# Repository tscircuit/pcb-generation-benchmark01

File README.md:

# PCB Generation Benchmark

Project scaffold for a paired dataset comparing three ways of producing PCB designs from the same prompts:

| Method ID | Workflow | Primary artifacts |
| --- | --- | --- |
| `tscircuit-codegen` | Generate tscircuit source code | Source, dependency lockfile, build outputs |
| `kicad-codegen` | Generate KiCad files directly or through recorded scripts/APIs | Native project, schematic, PCB, generation scripts |
| `kicad-computer-use` | Create and edit designs through KiCad's GUI | Native project, schematic, PCB, screenshots and action trace |

**Status: 10 draft prompts and a completed two-method generation pilot.** The [prompt catalog](prompts/README.md) includes easy, medium, and hard prompts with topic labels. The [pilot results](reports/2026-09-05-codegen-pilot-01/README.md) contain 20 generated schematic/PCB outcomes, retained candidates, previews, and raw validation reports. Computer use was excluded at the user’s request. Some generated designs have failing checks or unverified requirements; execution completion is not design acceptance. A deterministic rule scorer is implemented; reusable generation adapters/runner and scoring calibration remain future work.

## Layout

```text
prompts/                 Shared prompt catalog and per-prompt assets
configs/                 Experiment and environment templates
methods/                 Workflow contracts for the three methods
schemas/                 Record conventions for future validators
templates/               Copyable prompt, run, and evaluation records
data/runs/               Raw runs, organized by experiment/prompt/method/replicate
data/evaluations/        Separate evaluation records linked to run IDs
data/releases/           Future versioned dataset manifests
src/adapters/            Reserved for method implementations
src/runner/              Reserved for orchestration
src/evaluation/          Reserved for scoring and artifact inspection
scripts/                 Reserved for future commands
tests/                   Reserved for future validation tests
reports/                 Comparison reports and figures
docs/                    Protocol, dataset card, implementation roadmap
work/                    Ignored scratch space
```

## Start here

1. Read `docs/protocol.md` and `docs/roadmap.md`.
2. Copy `templates/prompt/` into `prompts/items/<prompt-id>/`, replace placeholders, and add the ID to `prompts/catalog.json`.
3. Copy `configs/experiment.template.json` to a named experiment configuration. Freeze its prompt revisions, model, budgets, tools, and repeat count before collecting data.
4. When the runner exists, collect each prompt across all three methods using `templates/run/`. Store evaluations separately using `templates/evaluation.template.json`.

Template files are examples of structure, not actual dataset entries. Cataloged prompts are drafts awaiting review. Do not report placeholder metrics as measurements. The recorded pilot uses installed tools and isolated generation tasks; reusable automation and full benchmark collection remain future work.

## Deterministic scoring

The [scoring implementation](docs/deterministic-scoring.md) evaluates frozen artifacts with versioned rules and fixed 30/30/20/20 weights. [Pilot scoring results](reports/2026-09-05-codegen-pilot-01/scoring.md) include per-rule evidence, critical failures, unknowns and possible score bounds. Run `bun run score -- 2026-09-05-codegen-pilot-01` to reproduce them. Missing evidence remains null; no model judge is called.

## Historical model-judge proposal

See `docs/model-judging.md` for the model-judge plan, `evaluation/rubric.json` for scoring rules, and `configs/judge.template.json` for fixed judge settings. Judgment and baseline-comparison templates record evidence, repeated scores, and improvement/regression decisions. The model judge and baseline-comparison flow remain scaffolds; deterministic scoring is implemented separately as described above.

## Pilot results

Start with the [results and PCB previews](reports/2026-09-05-codegen-pilot-01/README.md). The [frozen configuration](configs/2026-09-05-codegen-pilot-01.json) and [execution notes](data/runs/2026-09-05-codegen-pilot-01/execution-notes.json) record tool versions, budgets, the GUI exclusion, and context limitations. Eighteen runs used fresh subagents; two were generated by the parent after a hard agent limit. No comparative quality score is claimed.

Regenerate the file inventory and check prompt hashes/pair completeness with `bun run collect -- 2026-09-05-codegen-pilot-01 --require-complete`. This inventories existing artifacts and does not rerun generation.

## Git and storage

Track prompts, configs, native design files, code, and compact evidence. Do not commit secrets. Large recordings should use an explicitly selected external store or Git LFS when configured; record their URI and SHA-256 in the run manifest. Neither external storage nor LFS is configured yet. Dataset and code licensing remain undecided; see `docs/dataset-card.md`.

## Development with TypeScript and Bun

All active repository code runs with Bun. Install locked dependencies with `bun install --frozen-lockfile`.

- `bun run typecheck` — check TypeScript.
- `bun test` — scoring, geometry, artifact readers, archive integrity, saved-result parity, and website checks. Website checks use the existing generated bundle; run `bun run build` first after a clean checkout.
- `bun run rules` — verify/reproduce the ten frozen v1 rule specifications.
- `bun run score -- 2026-09-05-codegen-pilot-01` — evaluate retained artifacts into a new immutable TypeScript evaluation archive.
- `bun run collect -- 2026-09-05-codegen-pilot-01 --require-complete` — inventory existing runs.
- `bun run build` — render PCB layers and build the website.
- `bun run website:publish` — build and replace the existing public website using `ohmx-box`.

The PCB renderer calls the native KiCad CLI (`KICAD_CLI` or `kicad-cli` on PATH). Hosting uses the existing `ohmx-box` CLI. These are external tools, not Python repository scripts. Historical generation scripts and archived Python evaluator sources remain unchanged under `data/` for reproducibility. Canonical prompts and frozen run inputs also remain unchanged.

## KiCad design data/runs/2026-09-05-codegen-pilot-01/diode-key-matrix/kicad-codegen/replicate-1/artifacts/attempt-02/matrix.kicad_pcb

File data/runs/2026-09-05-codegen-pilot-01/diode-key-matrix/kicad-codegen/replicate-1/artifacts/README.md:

# Nine-key diode-isolated matrix

Entry files: `attempt-03/matrix.kicad_pro`, `attempt-03/matrix.kicad_sch`, and `attempt-03/matrix.kicad_pcb`. `generate.py` is the editable generation source. Open native files directly in KiCad. Attempt-01 and attempt-02 are preserved historical candidates, including the initial crossing failure. Native SVG and netlist exports are retained per candidate.

Method: Python generated the schematic S-expression using embedded standard KiCad symbols, and KiCad 10.0.6 pcbnew bindings generated the placed/routed two-layer board. No GUI, tscircuit, reference design, or external benchmark artifacts were used. The libraries used are bundled KiCad standard libraries; subsets are included for portability.

Components: nine generic normally-open 6 mm tactile switches with the standard `Button_Switch_THT:SW_PUSH_6mm` footprint. Its two pad-1 terminals form one electrical terminal and its two pad-2 terminals form the other; both copies are explicitly routed on the board. Diodes are 1N4148 in DO-35, using `Diode_THT:D_DO-35_SOD27_P7.62mm_Horizontal`: pad 1 = cathode (K, body stripe), pad 2 = anode (A). The footprint includes cathode stripe and K silkscreen markings. J1 is a straight 2.54 mm through-hole 1×6 header, with a rectangular pin-1 pad, individual pin numbers, and a signal legend. J1 pins 1–6 are ROW1, ROW2, ROW3, COL1, COL2, COL3.

Every COL connects switch terminal 1; terminal 2 connects its dedicated diode anode through KEYrc; diode cathode connects ROWr. No pull-ups or controller are added. The 65×65 mm outline has its lower-left at native coordinate (0,65). Native y increases downwards, so switch centres are (12,53), (32,53), (52,53), etc.; measured from lower-left they are the requested Cartesian grid. All diode body centres are 6.5 mm below their respective switches. Traces are 0.30 mm and clearance is constrained to at least 0.25 mm through project rules and an explicit `.kicad_dru` rule.

Validation: final native ERC has 0 errors and 38 library warnings; DRC has 0 errors, 19 library warnings, and 0 unconnected pads. Native schematic parity reports 0 issues. Independent source-side geometry and pin-net checks pass; raw logs are under `../logs/`. Strict warning-inclusive checks are not clean. KiCad 10.0.6 reports the included sym-lib-table/fp-lib-table as UNINITIALIZED and skips them; embedded native symbol and footprint data nevertheless export and validate. Library browsing/relinking may require re-registering the included subset libraries. No further repair was attempted after the permitted two repairs.

No manufacturing or physical tests were performed. Generic tactile switch vendor selection is left open; select a switch matching the documented 6.5×4.5 mm pad arrangement. No GUI or rendered-image visual inspection was performed; SVG exports are available for inspection.

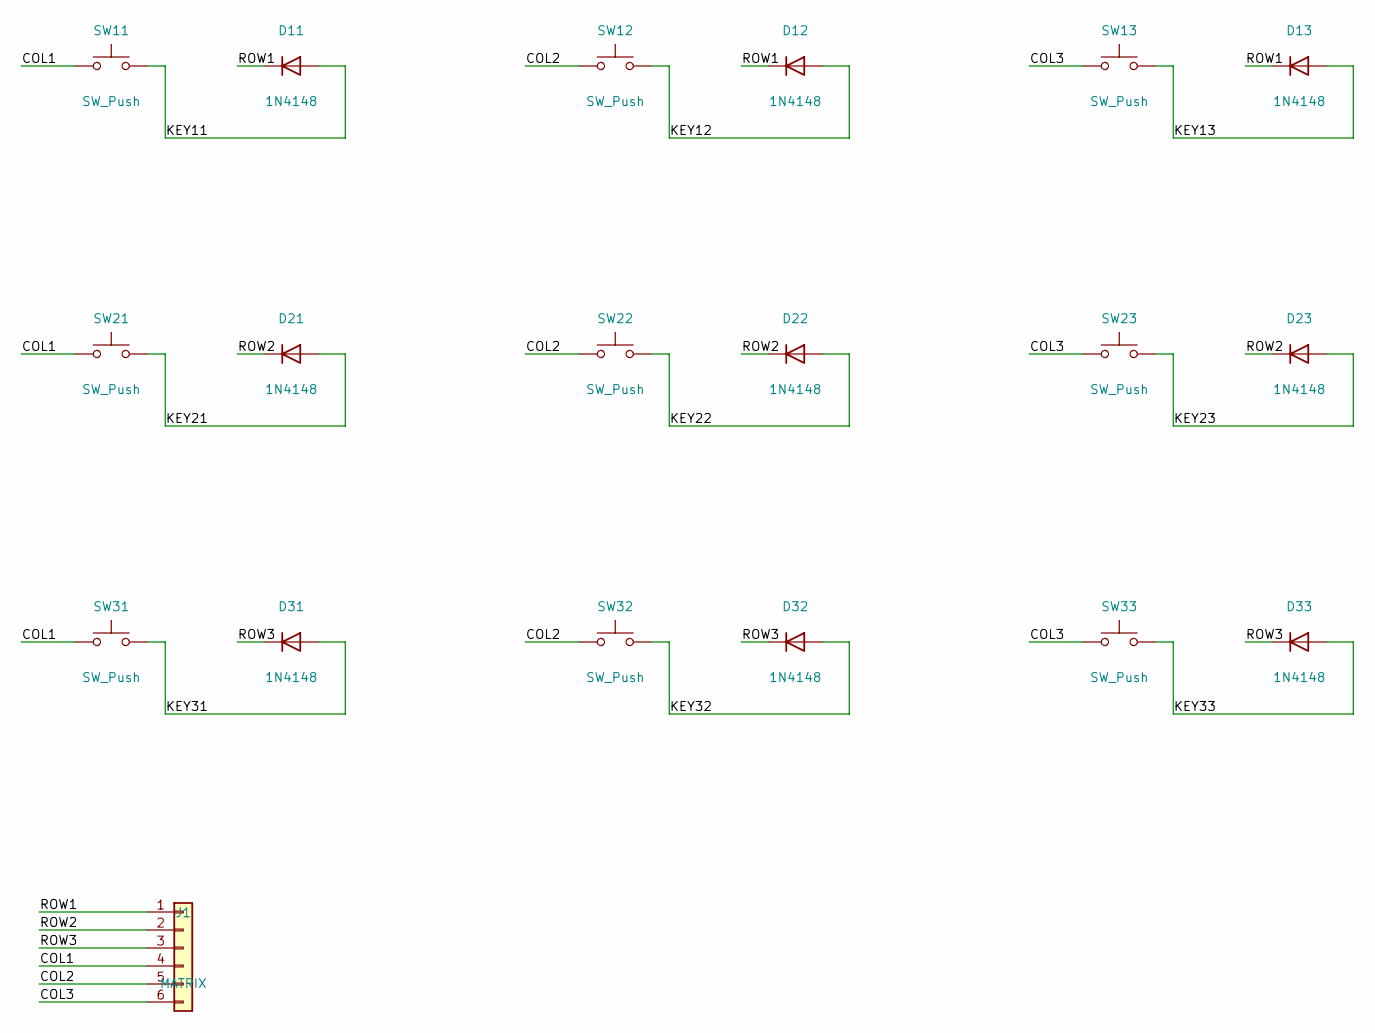
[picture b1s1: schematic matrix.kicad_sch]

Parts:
D11, D12, D13, D21, D22, D23, D31, D32, D33: 1N4148; D_DO-35_SOD27_P7.62mm_Horizontal
J1: MATRIX; PinHeader_1x06_P2.54mm_Vertical
SW11, SW12, SW13, SW21, SW22, SW23, SW31, SW32, SW33: SW_Push; SW_PUSH_6mm

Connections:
/COL1: J1.4, SW11.1, SW21.1, SW31.1
/COL2: J1.5, SW12.1, SW22.1, SW32.1
/COL3: J1.6, SW13.1, SW23.1, SW33.1
/KEY11: D11.2 (A), SW11.2
/KEY12: D12.2 (A), SW12.2
/KEY13: D13.2 (A), SW13.2
/KEY21: D21.2 (A), SW21.2
/KEY22: D22.2 (A), SW22.2
/KEY23: D23.2 (A), SW23.2
/KEY31: D31.2 (A), SW31.2
/KEY32: D32.2 (A), SW32.2
/KEY33: D33.2 (A), SW33.2
/ROW1: D11.1 (K), D12.1 (K), D13.1 (K), J1.1
/ROW2: D21.1 (K), D22.1 (K), D23.1 (K), J1.2
/ROW3: D31.1 (K), D32.1 (K), D33.1 (K), J1.3

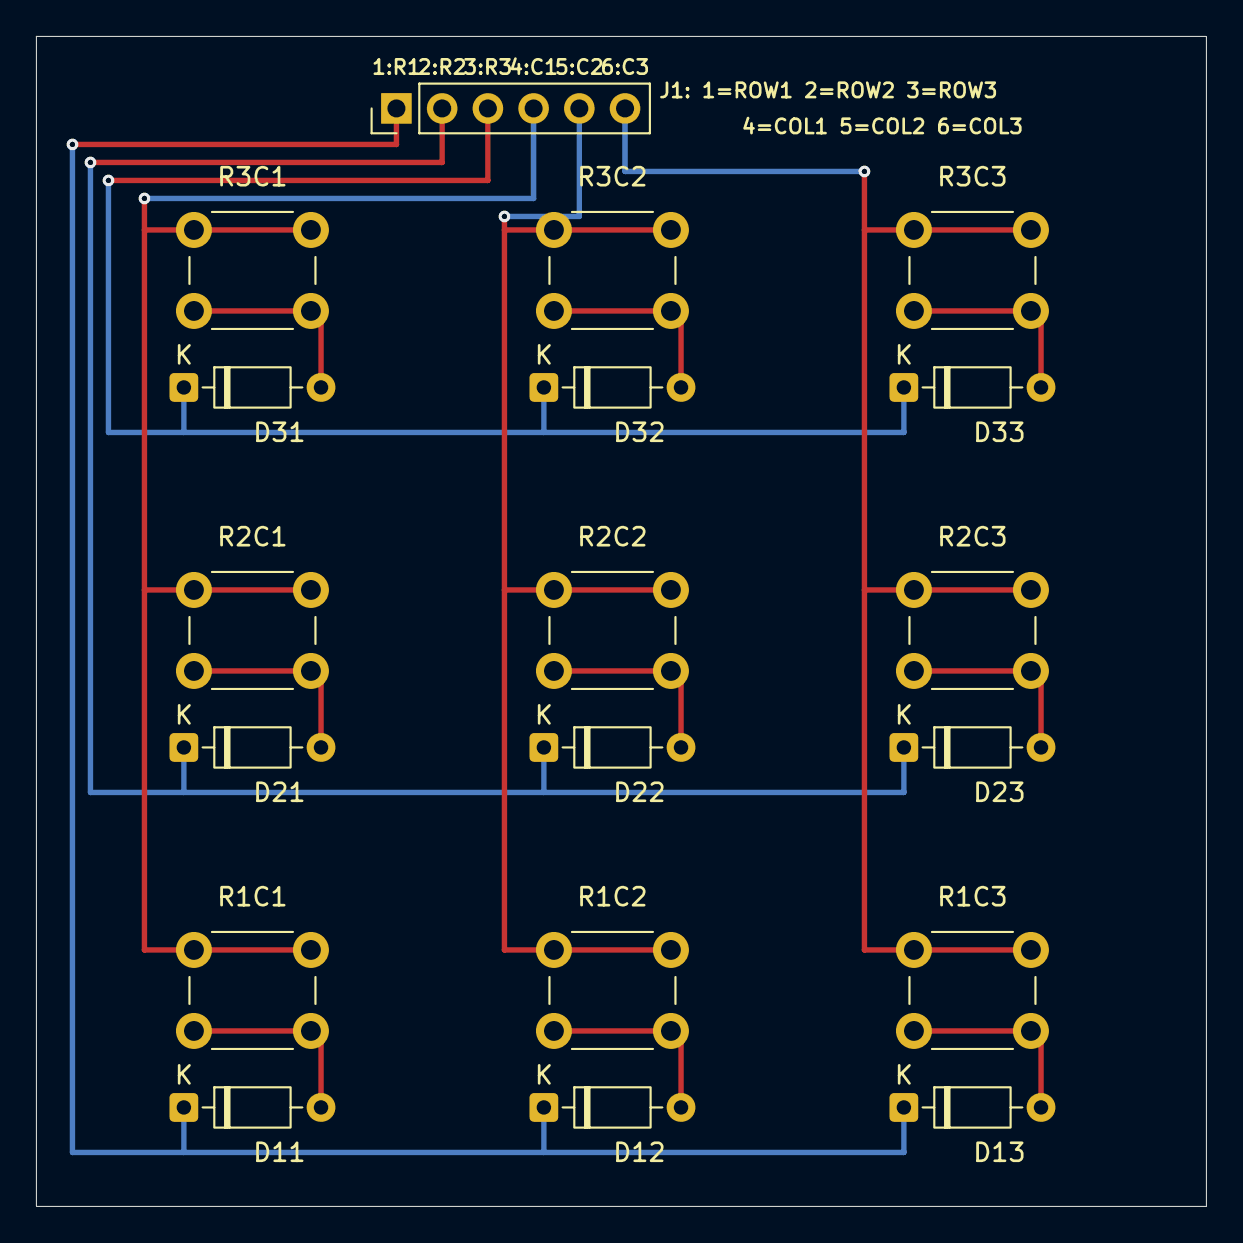
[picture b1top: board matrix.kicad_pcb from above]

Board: 2 copper layers, 65.0 x 65.0 mm, 19 parts (0 on the bottom side), 15 nets.

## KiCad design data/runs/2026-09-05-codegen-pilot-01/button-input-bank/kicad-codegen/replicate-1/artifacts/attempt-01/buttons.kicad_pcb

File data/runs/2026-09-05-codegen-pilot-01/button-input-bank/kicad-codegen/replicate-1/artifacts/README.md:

# Four-button digital input board

Final entry files: `attempt-03/buttons.kicad_pro`, `attempt-03/buttons.kicad_sch`, and `attempt-03/buttons.kicad_pcb`. The editable generation source is `attempt-03/generate.py`; it uses the KiCad 10.0.6 bundled pcbnew Python API for the board and writes a native schematic containing embedded standard KiCad symbols. No GUI, tscircuit, reference design, or downloaded design was used.

The board outline runs from (0,0) to (50,35) mm and has two copper layers. All routes use 0.30 mm traces with project minimum clearance and trace width set to 0.25 mm. Switch centers are 11 mm apart in a horizontal row. J1 is a standard 2.54 mm through-hole six-pin header: 1=+3V3, 2=GND, 3=BTN1, 4=BTN2, 5=BTN3, 6=BTN4. Its square pad and explicit `1:+3V3` silkscreen identify pin 1; all signals are marked.

R1–R4 use KiCad `Device:R` and `Resistor_SMD:R_0805_2012Metric`, 10 kohm. Pin 1 is +3V3 and pin 2 is its BTN signal. C1–C4 use `Device:C` and `Capacitor_SMD:C_0805_2012Metric`, 100 nF; pin 1 is BTN and pin 2 GND. SW1–SW4 use `Switch:SW_Push` and `Button_Switch_THT:SW_PUSH_6mm`, representing normally-open 6 mm momentary switches. Both footprint pads numbered 1 connect to BTN and both pads numbered 2 connect to GND. Use switches whose datasheet matches this standard terminal arrangement; no manufacturer part number was selected. Both duplicated terminal pairs are explicitly routed.

Attempt 01 is retained unchanged with 13 ERC library-configuration warnings and 15 PCB warnings. Attempt 02 adds a local symbol table, enlarges silkscreen, and trims a dangling ground rail; four capacitor silkscreen overlap warnings remain. Attempt 03 moves those labels; native ERC and DRC including schematic parity report zero violations and zero unconnected pads. Standard KiCad default ignored checks are visible in the raw reports; no violations were manually excluded. Native schematic netlist and SVG exports and PCB SVG export succeeded. `logs/attempt-03/connectivity-and-geometry.json` records an independent schematic/PCB pin-map check and dimensions. The 50.05 by 35.05 mm bounding box includes the 0.05 mm outline stroke; outline centerlines are exactly 50 by 35 mm.

Validation scripts and exact output are under `logs/attempt-01` through `logs/attempt-03`. Library tables use installed absolute KiCad library paths; edit those tables on a different machine. Embedded symbols and footprints remain editable without those paths. No manufacturing exports or physical tests were requested or performed. SVGs were exported but not visually inspected; electrical/layout validation is based on native checks and programmatic geometry/connectivity checks.

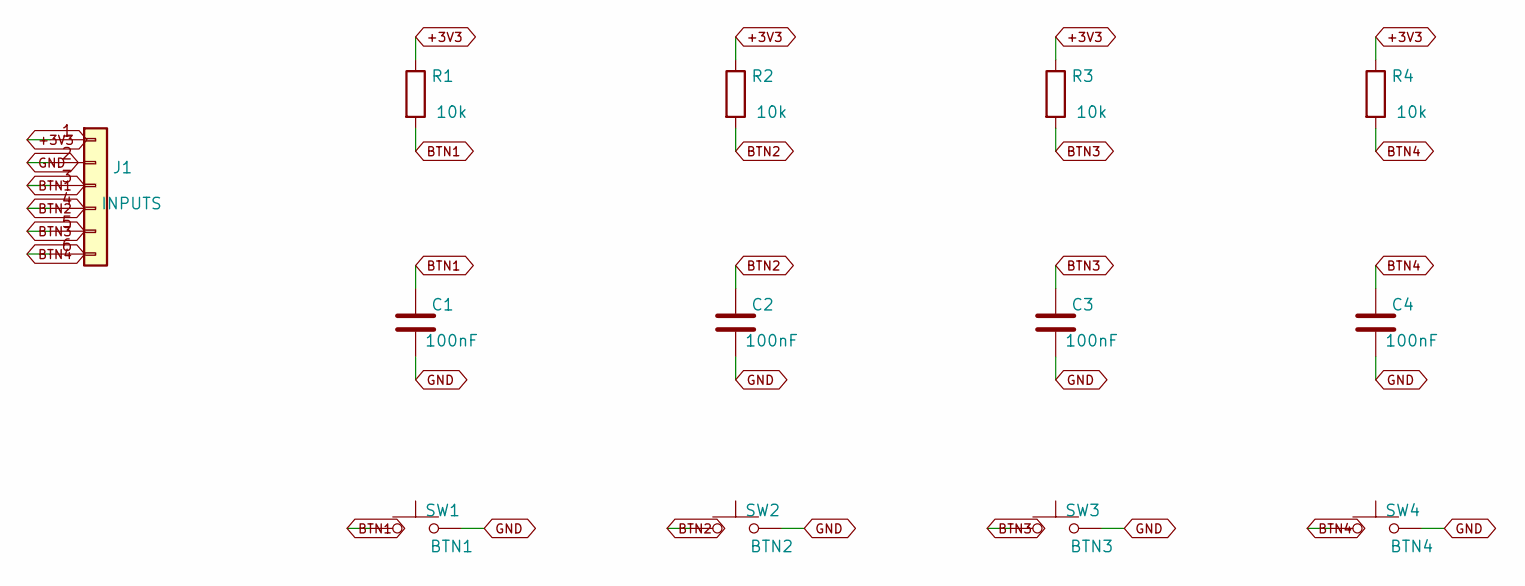
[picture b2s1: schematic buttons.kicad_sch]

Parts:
C1, C2, C3, C4: 100nF; C_0805_2012Metric
J1: INPUTS; PinHeader_1x06_P2.54mm_Vertical
R1, R2, R3, R4: 10k; R_0805_2012Metric
SW1: BTN1; SW_PUSH_6mm
SW2: BTN2; SW_PUSH_6mm
SW3: BTN3; SW_PUSH_6mm
SW4: BTN4; SW_PUSH_6mm

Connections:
+3V3: J1.1, R1.1, R2.1, R3.1, R4.1
BTN1: C1.1, J1.3, R1.2, SW1.1
BTN2: C2.1, J1.4, R2.2, SW2.1
BTN3: C3.1, J1.5, R3.2, SW3.1
BTN4: C4.1, J1.6, R4.2, SW4.1
GND: C1.2, C2.2, C3.2, C4.2, J1.2, SW1.2, SW2.2, SW3.2, SW4.2

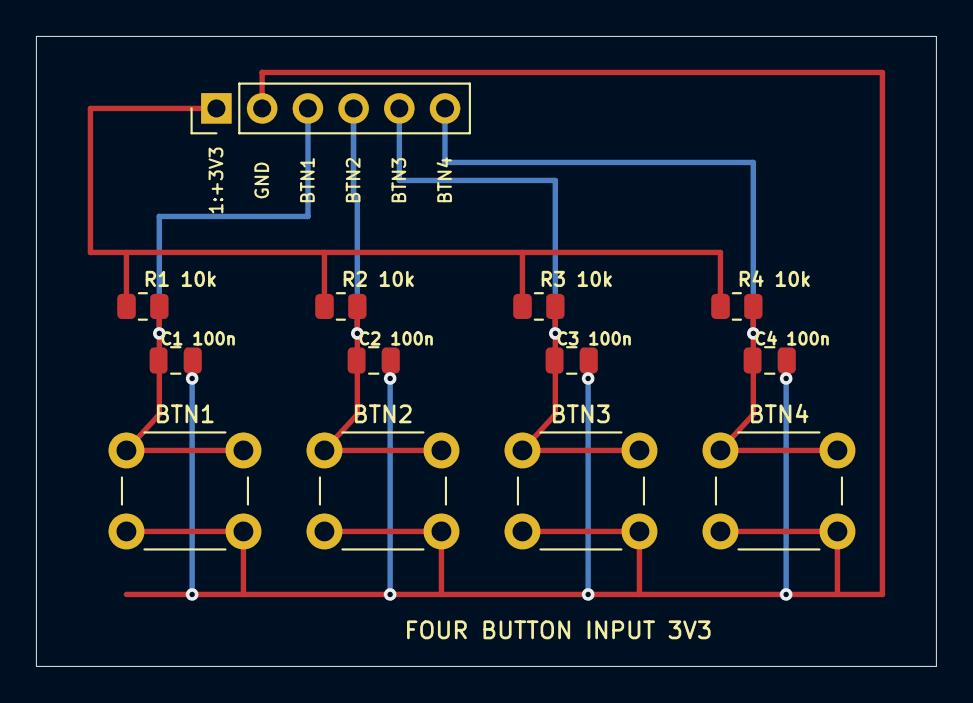
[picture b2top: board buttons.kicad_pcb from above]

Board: 2 copper layers, 50.0 x 35.0 mm, 13 parts (0 on the bottom side), 6 nets.

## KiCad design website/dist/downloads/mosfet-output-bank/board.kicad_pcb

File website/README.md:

# PCB benchmark comparison website

Static presentation of the preserved two-method pilot. Build the derived PCB views with `bun run website:views`, then run `bun run website:build` from the repository root. The build reads the pinned evaluation and frozen prompt inputs; it does not run generation or scoring.

Publish with `ohmx-box publish-html --json website/dist --title 'PCB Generation Benchmark 01'`. For an intentional update to that existing website, add `--replace`.

Public URL: https://0hmx.com/artifacts/pcb-generation-benchmark-01/

The publication bundle contains only the generated HTML/CSS, selected result fields, recorded previews and final native KiCad files. Nineteen previews were recorded; the KiCad I2C hub preview is unavailable. Sanitized supplementary transcripts include recorded tool output and relevant local paths; full session archives are not included. The comparison and downloadable results show recorded DRC status and reports, without numeric scores. Missing DRC remains unknown; tscircuit placement and shorts checks are not relabeled as full DRC. Historical evaluations remain preserved.

Each KiCad design offers original schematic, PCB and project downloads plus a ZIP. `download-manifest.json` records source paths and SHA-256 checksums; published native bytes match the retained final attempts.

PCB viewers use read-only KiCad 10 per-layer SVG exports and preserved tscircuit SVG layer data. All displayed layers start at 50% opacity, with zoom, pan, visibility and opacity controls. `dist/views/manifest.json` records sources and hashes. Original previews, design files and scores are preserved. Rendering uses `KICAD_CLI` or `kicad-cli` on PATH.

The comparison layout targets desktop: two persistent columns, up to 1840px of page width, and 640px tall viewers. Explicit iframe dimensions prevent fallback to the browser's 300×150 default. Stylesheet and viewer URLs include content hashes to prevent stale cached layouts after updates.

The tscircuit previews now use `@tscircuit/pcb-viewer` 1.11.393 directly with byte-for-byte copies of each final `circuit.json`. `tscircuit-viewer.tsx` mounts the native React viewer with editing disabled and adds opacity controls over the package's `.pcb-layer-*` canvases. Those presentation hooks are version-pinned; the native toolbar remains available for measurements and overlays. Bun bundles the viewer locally, without CDN dependencies.

KiCad continues to use native CLI SVG exports. Its controls include layer visibility, per-layer opacity, solo mode, front/back/copper presets, wheel zoom, pan, fit, and fullscreen. Clicking a drawn shape or stroked text selects that drawing item for independent opacity or hiding. This selection is a drawing item, not a semantic KiCad component. Item opacity multiplies layer opacity; restoring items and resetting layers are separate controls. None of these controls edits benchmark design files.

`website/dist/` is generated output and is ignored by Git. Run `bun run build` to recreate it before website validation or publication. The source files, recorded benchmark inputs, and package lockfile are tracked.
## Timing and recovered chats

The table and design cards display each original `run.json` total duration in seconds. A null duration can have a separately labeled `ended_at - started_at` derived total; raw records stay unchanged. The tscircuit voltage divider is the sole such run in this pilot (265.941775 seconds). Generation-only duration is unavailable for every run. Total run windows include validation and repairs and are not isolated generation measurements. JSON retains full precision; HTML rounds to milliseconds.

Every run links to a readable transcript page and its supplementary JSON evidence. All 20 transcripts are **incomplete**: 18 dedicated sessions have encrypted delegation content, and two parent-generated runs have conservatively attributed excerpts. Each export records source archive SHA-256, source line numbers and hashes, session identity, mapping evidence, frozen input hashes and recorded attempts. Hidden reasoning, encrypted payloads and credentials are excluded; binary media is represented by hashes. Tool outputs retain any original truncation. These files are supplementary evidence, not revised benchmark records or scores.

Recovery is an explicit local operation, never part of the website build:

```sh
bun scripts/recover-generation-transcripts.ts /path/to/local/session/archives
bun run website:build
```

The build uses only checked-in supplementary evidence and does not require local chats. Export files use content-hashed names and are never overwritten. `data/supplementary/2026-09-05-codegen-pilot-01/transcripts/index.json` selects current exports. Exact extractor/sanitizer snapshots are retained in `extractors/` by SHA-256. Archive line hashes cover the original UTF-8 JSON line without its newline. Full original session archives remain local and are not distributed. Public transcript JSON has its own content hash after exclusion/redaction.

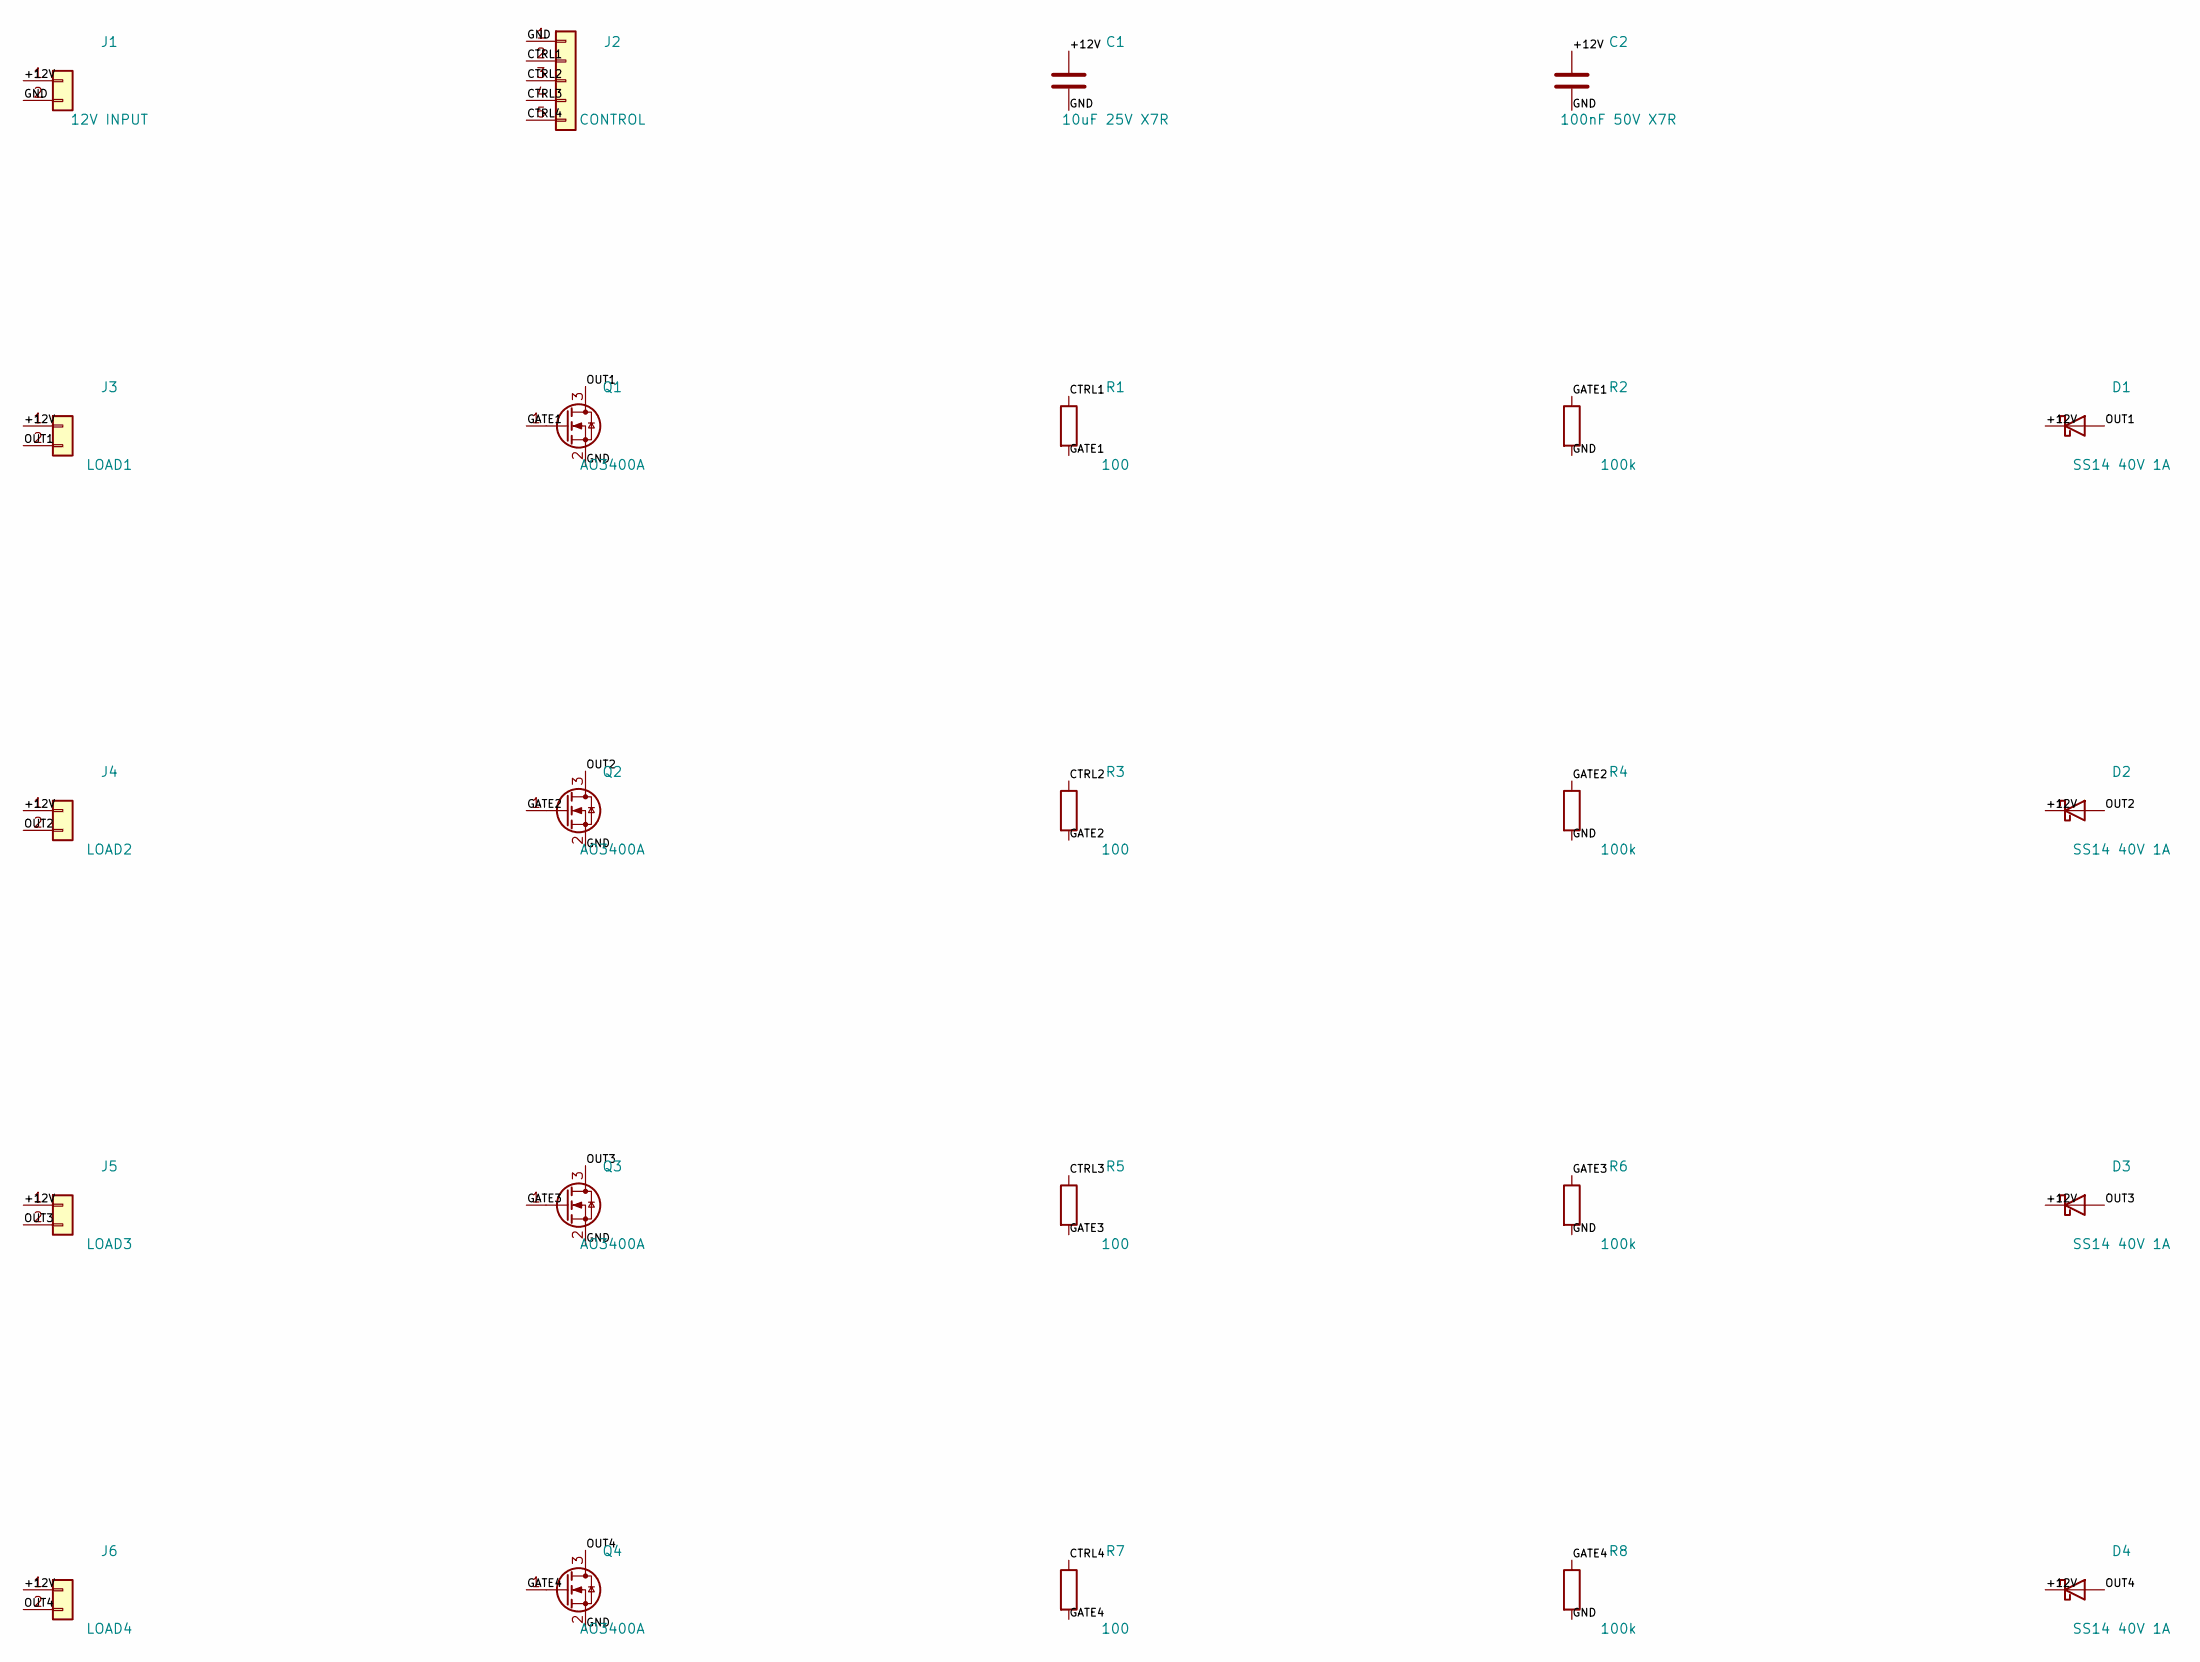
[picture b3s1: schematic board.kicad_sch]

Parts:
C1: 10uF 25V X7R; C_0805_2012Metric
C2: 100nF 50V X7R; C_0805_2012Metric
D1, D2, D3, D4: SS14 40V 1A; D_SMA
J1: 12V INPUT; PinHeader_1x02_P2.54mm_Vertical
J2: CONTROL; PinHeader_1x05_P2.54mm_Vertical
J3: LOAD1; PinHeader_1x02_P2.54mm_Vertical
J4: LOAD2; PinHeader_1x02_P2.54mm_Vertical
J5: LOAD3; PinHeader_1x02_P2.54mm_Vertical
J6: LOAD4; PinHeader_1x02_P2.54mm_Vertical
Q1, Q2, Q3, Q4: AO3400A; SOT-23
R1, R3, R5, R7: 100; R_0805_2012Metric
R2, R4, R6, R8: 100k; R_0805_2012Metric

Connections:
/+12V: C1.1, C2.1, D1.1 (K), D2.1 (K), D3.1 (K), D4.1 (K), J1.1, J3.1, J4.1, J5.1, J6.1
/CTRL1: J2.2, R1.1
/CTRL2: J2.3, R3.1
/CTRL3: J2.4, R5.1
/CTRL4: J2.5, R7.1
/GATE1: Q1.1 (G), R1.2, R2.1
/GATE2: Q2.1 (G), R3.2, R4.1
/GATE3: Q3.1 (G), R5.2, R6.1
/GATE4: Q4.1 (G), R7.2, R8.1
/GND: C1.2, C2.2, J1.2, J2.1, Q1.2 (S), Q2.2 (S), Q3.2 (S), Q4.2 (S), R2.2, R4.2, R6.2, R8.2
/OUT1: D1.2 (A), J3.2, Q1.3 (D)
/OUT2: D2.2 (A), J4.2, Q2.3 (D)
/OUT3: D3.2 (A), J5.2, Q3.3 (D)
/OUT4: D4.2 (A), J6.2, Q4.3 (D)

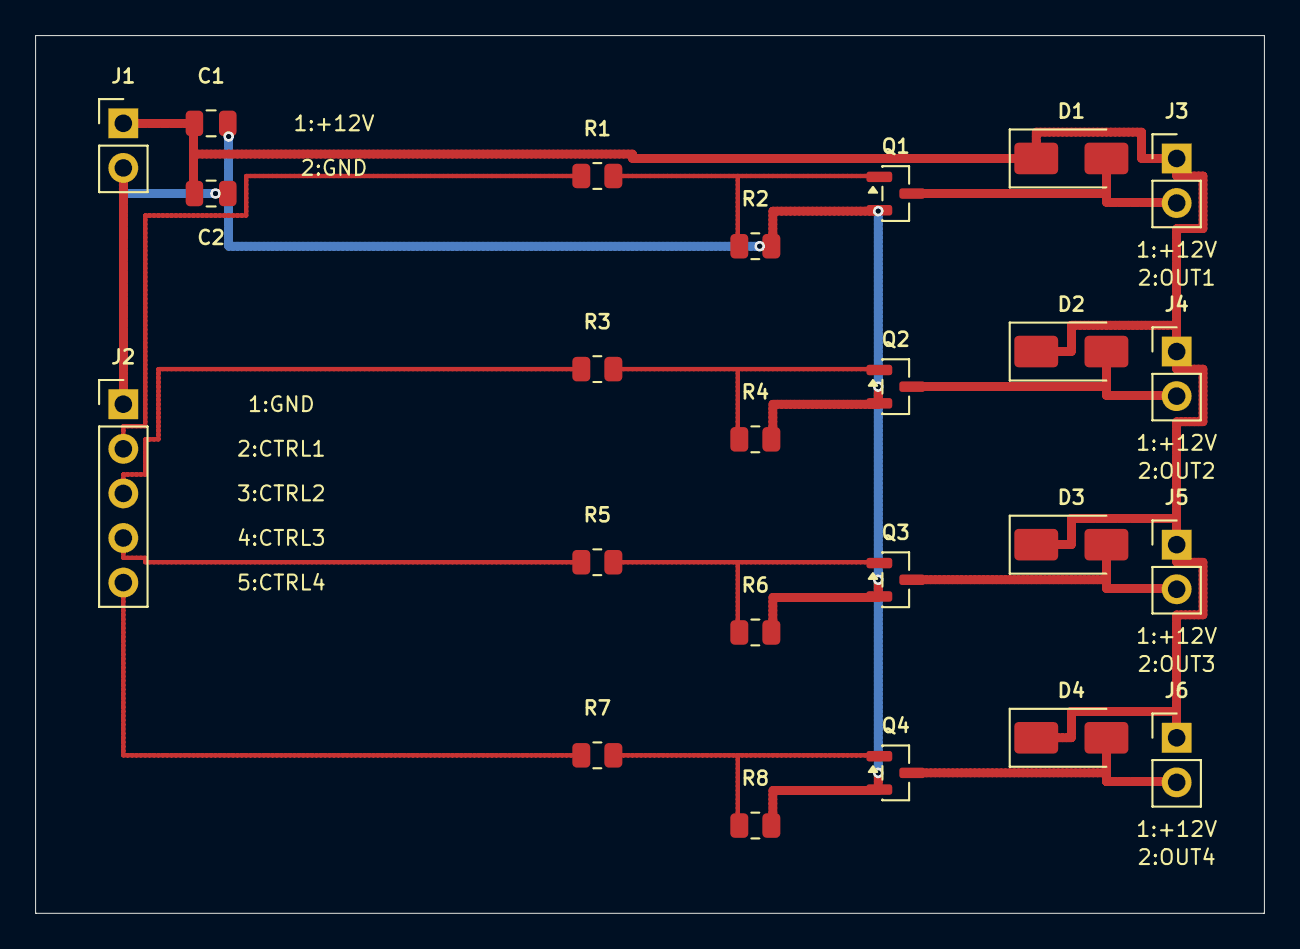
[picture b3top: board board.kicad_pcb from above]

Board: 2 copper layers, 70.0 x 50.0 mm, 24 parts (0 on the bottom side), 14 nets.

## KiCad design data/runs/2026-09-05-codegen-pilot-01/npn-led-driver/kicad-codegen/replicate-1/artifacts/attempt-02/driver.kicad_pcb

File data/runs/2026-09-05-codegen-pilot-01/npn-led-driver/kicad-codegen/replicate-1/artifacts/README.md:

# Two-channel transistor LED driver

Final entry: `attempt-03/driver.kicad_pro`, with editable `driver.kicad_sch` and fully routed `driver.kicad_pcb`. The final folder includes the selected standard KiCad symbols and footprints and relative library tables. `generate.py` is the editable generation source (requires the installed KiCad Python runtime and standard library paths shown in the script). SVG exports provide inspection views; native files are authoritative.

The method used direct KiCad schematic text generation and the KiCad 10.0.6 Python PCB API, with a two-layer grid router written for this run. No GUI, external board designs, or benchmark references were used. Three distinct candidates are retained. Attempt 01 had clearance, silkscreen, drill-spacing and schematic configuration/grid issues. Attempt 02 repaired these. Attempt 03 added symbol-to-footprint UUID links, complete footprint identifiers, a specific transistor ordering code and portable local libraries. Original reports and unsuccessful export commands are preserved; the export invocation was subsequently corrected without changing candidate files.

## Circuit and parts

- J1: 1×4, 2.54 mm through-hole header; pin 1 +5V, 2 GND, 3 CTRL1, 4 CTRL2. Square pad 1 and explicit `1 +5V` silkscreen identify orientation; other signals are on silkscreen.
- Q1/Q2: onsemi MMBT3904LT1G, SOT-23. Datasheet page 1 identifies pin 1 base, pin 2 emitter, pin 3 collector. The selected KiCad `Q_NPN_BEC` symbol has precisely this numbering; the `Package_TO_SOT_SMD:SOT-23` footprint has 1 and 2 on the two-pad side and 3 on the opposite side. Base is BASE1/BASE2, emitter GND and collector COL1/COL2. Manufacturer source: https://www.onsemi.com/pdf/datasheet/mmbt3904lt1-d.pdf (preserved under logs, with extracted text).
- D1/D2: red 0805 LEDs, standard `LED_0805_2012Metric`; pad 1 cathode to collector, pad 2 anode to 1 kΩ resistor. A specific LED manufacturer ordering code was not selected.
- R1/R4: 1 kΩ +5V-to-anode resistors. R2/R5: 4.7 kΩ CTRL-to-base resistors. R3/R6: 100 kΩ base-to-GND resistors. All are standard 0805.
- C1: 100 nF, standard 0805, between +5V and GND.

Outline centre lines are (50,50) to (95,80) mm: 45×30 mm; copper layers F.Cu/B.Cu. Edge bounding box including the 0.05 mm stroke measures 45.05×30.05 mm. D1/D2 centres are 15 mm apart. C1 centre is 4.00045 mm from the centroid of J1's four pads. Tracks are 0.25 mm wide; configured clearance is 0.25 mm. All components are inside the outline. No manufacturing or physical tests were requested or performed.

## Validation and unresolved issues

Final ERC: 0 errors, 0 warnings. Standard PCB DRC: 0 violations, 0 unconnected pads, 0 footprint errors. Native schematic netlist and SVG exports and PCB SVG export succeeded. Raw logs are in the run-level `logs/` folder, notably `attempt-03-erc.rpt`, `attempt-03-drc.rpt`, and `attempt-03-connectivity.json`.

The additional native `--schematic-parity` check failed with 28 net-name warnings: schematic local labels export as `/NET`, while PCB nets are named `NET`. An independent pin-group comparison, removing only this leading slash, confirms all 28 pins on all 10 nets exactly match both the schematic and intended pin map. This is a real naming inconsistency, retained because the maximum two repaired candidates were already used. Synchronizing the project in KiCad needs attention to these names.

The schematic uses named connections in a component grid. Inspection of the exported SVG found value/label overlap around transistors and LEDs; readability is imperfect even though connectivity is present and ERC passes. No circuit simulation or physical verification was performed. The final result is completed generation with documented limitations, not an unconditional correctness claim.

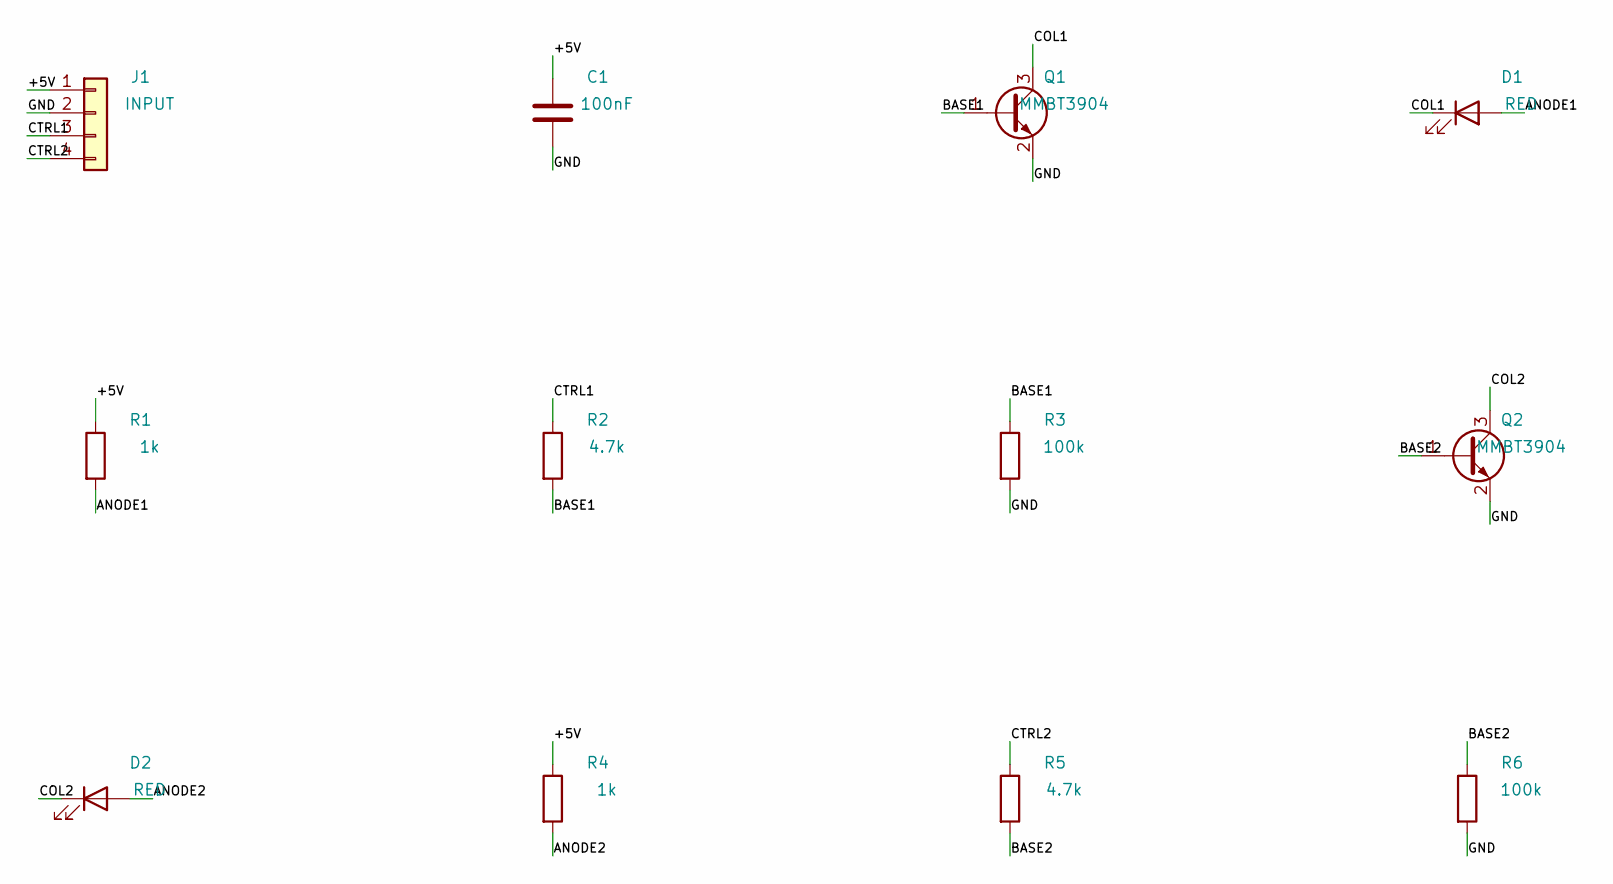
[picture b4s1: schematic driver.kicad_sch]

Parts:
C1: 100nF; C_0805_2012Metric
D1, D2: RED; LED_0805_2012Metric
J1: INPUT; PinHeader_1x04_P2.54mm_Vertical
Q1, Q2: MMBT3904; SOT-23
R1, R4: 1k; R_0805_2012Metric
R2, R5: 4.7k; R_0805_2012Metric
R3, R6: 100k; R_0805_2012Metric

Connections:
+5V: C1.1, J1.1, R1.1, R4.1
ANODE1: D1.2 (A), R1.2
ANODE2: D2.2 (A), R4.2
BASE1: Q1.1 (B), R2.2, R3.1
BASE2: Q2.1 (B), R5.2, R6.1
COL1: D1.1 (K), Q1.3 (C)
COL2: D2.1 (K), Q2.3 (C)
CTRL1: J1.3, R2.1
CTRL2: J1.4, R5.1
GND: C1.2, J1.2, Q1.2 (E), Q2.2 (E), R3.2, R6.2

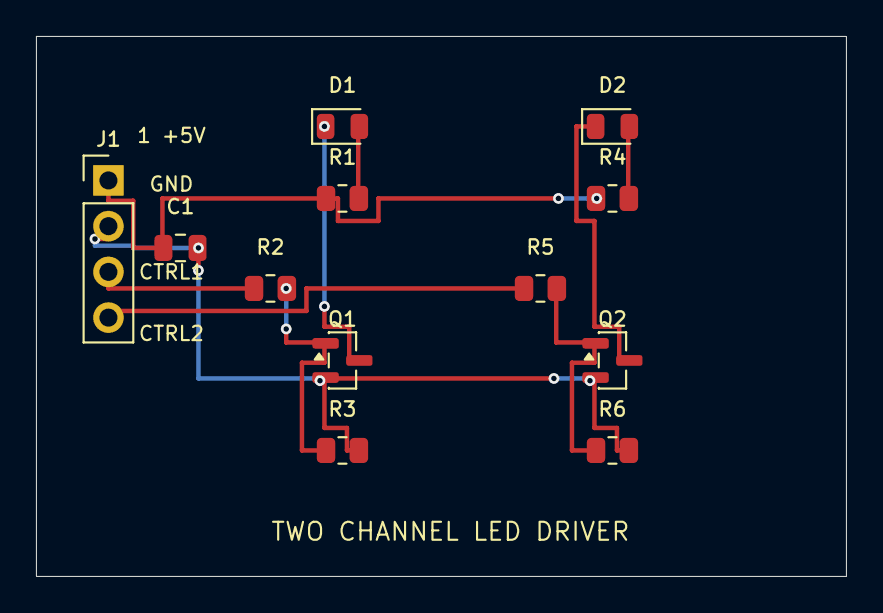
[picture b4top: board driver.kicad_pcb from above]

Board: 2 copper layers, 45.0 x 30.0 mm, 12 parts (0 on the bottom side), 10 nets.

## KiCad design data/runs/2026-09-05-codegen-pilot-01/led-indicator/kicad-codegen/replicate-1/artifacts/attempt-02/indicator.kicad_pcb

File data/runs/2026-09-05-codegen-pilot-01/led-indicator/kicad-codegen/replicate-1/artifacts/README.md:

# LED power indicator — KiCad code generation

Final entry files: `attempt-03/indicator.kicad_pro`, `attempt-03/indicator.kicad_sch`, and `attempt-03/indicator.kicad_pcb`. The editable source generator is `attempt-03/generate.py`; its dependency is the installed KiCad 10 Python pcbnew binding. Native files open independently of the generator. Exact standard symbol/footprint dependencies are bundled in `attempt-03/libraries` with project-local library tables.

The rectangular board is 30 × 20 mm with F.Cu and B.Cu. All connections use 0.30 mm F.Cu tracks; B.Cu is available and unused. Project and custom rules enforce 0.25 mm clearance and minimum track width. J1 is a 2.54 mm through-hole 1×2 header, with pin 1 (+5V) at (103,108.73) mm and pin 2 (GND) at (103,111.27) mm. The header centre lies 3 mm from the left edge at x=100. D1's centre is (127,108.73), 3 mm from the right edge at x=130. All footprint bounds are inside the board.

R1 is a generic 1 kohm 0805 resistor: pad 1 +5V, pad 2 LED_A. D1 is a generic red 0805 LED: pad 1 cathode/GND and pad 2 anode/LED_A, matching KiCad's standard LED symbol and LED_0805_2012Metric footprint. J1 pin 1 is square and explicitly labelled `1 +5V`; pin 2 is labelled `2 GND`. The LED cathode has the standard footprint mark and additional `K` silkscreen. Actual LED ordering must use this pad polarity and package; no manufacturer part number was requested or selected.

The schematic contains real wires and named nets. KiCad exported its netlist and SVG successfully. Final native ERC found zero errors/warnings; final PCB DRC with schematic parity found zero violations, zero unconnected pads, and zero parity issues. Reports are `../logs/attempt-03-erc.rpt` and `../logs/attempt-03-drc.rpt`; exact validation commands and console output are alongside them. SVG exports supplement the editable native files.

Preserved attempts: attempt-01 stopped at a Python enum mismatch after creating its schematic; attempt-02 created the board but reported missing library registration and differing local net name prefixes; attempt-03 corrects those with bundled libraries and matching names. Attempt-02's first PCB SVG export also failed because a file output option was passed a directory; attempt-03 uses a filename. Every original candidate and diagnostic is retained.

Method: direct native schematic text generation using standard embedded KiCad symbols, and pcbnew API board generation; shell only, no GUI. The Python binding emitted a wxApp initialization assertion message but completed final generation; this raw message is retained. No manufacturing exports, physical testing, simulation, or manufacturer-specific LED qualification was performed. No unresolved requested layout or connectivity requirements were found by the recorded checks. ERC/DRC use KiCad's default check enablement as listed in the reports; no violation exclusions were added.

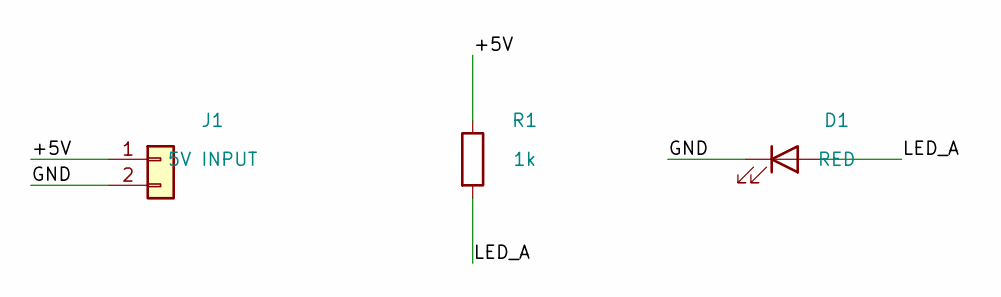
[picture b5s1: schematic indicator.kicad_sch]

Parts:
D1: RED; LED_0805_2012Metric
J1: 5V INPUT; PinHeader_1x02_P2.54mm_Vertical
R1: 1k; R_0805_2012Metric

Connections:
+5V: J1.1, R1.1
GND: D1.1 (K), J1.2
LED_A: D1.2 (A), R1.2

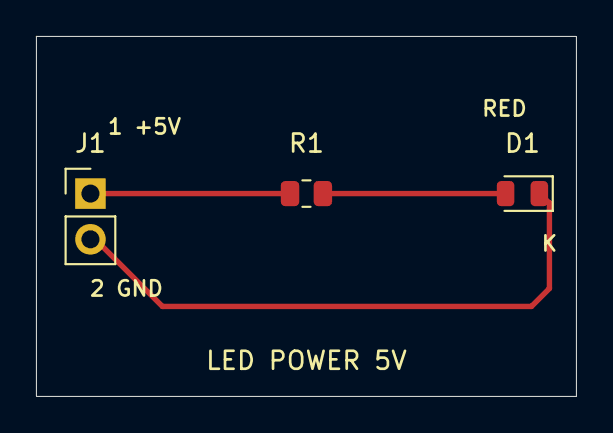
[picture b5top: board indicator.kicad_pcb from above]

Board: 2 copper layers, 30.0 x 20.0 mm, 3 parts (0 on the bottom side), 3 nets.

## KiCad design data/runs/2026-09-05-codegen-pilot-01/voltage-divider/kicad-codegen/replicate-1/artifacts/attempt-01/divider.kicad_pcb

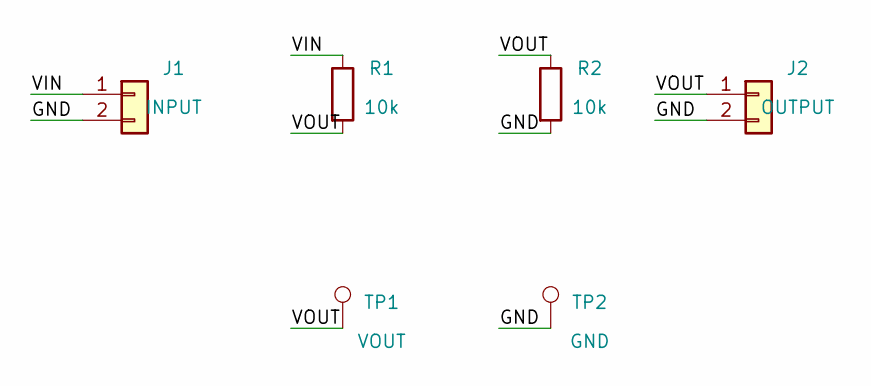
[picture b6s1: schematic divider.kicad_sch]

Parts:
J1: INPUT; PinHeader_1x02_P2.54mm_Vertical
J2: OUTPUT; PinHeader_1x02_P2.54mm_Vertical
R1, R2: 10k; R_0805_2012Metric
TP1: VOUT; TestPoint_Pad_D1.5mm
TP2: GND; TestPoint_Pad_D1.5mm

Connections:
/GND: J1.2, J2.2, R2.2, TP2.1
/VIN: J1.1, R1.1
/VOUT: J2.1, R1.2, R2.1, TP1.1

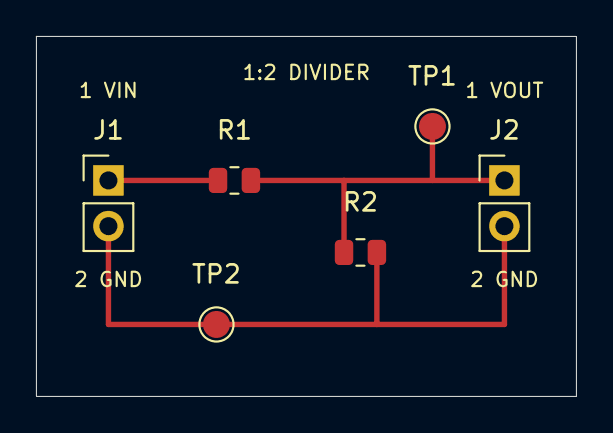
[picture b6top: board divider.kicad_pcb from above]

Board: 2 copper layers, 30.0 x 20.0 mm, 6 parts (0 on the bottom side), 3 nets.
